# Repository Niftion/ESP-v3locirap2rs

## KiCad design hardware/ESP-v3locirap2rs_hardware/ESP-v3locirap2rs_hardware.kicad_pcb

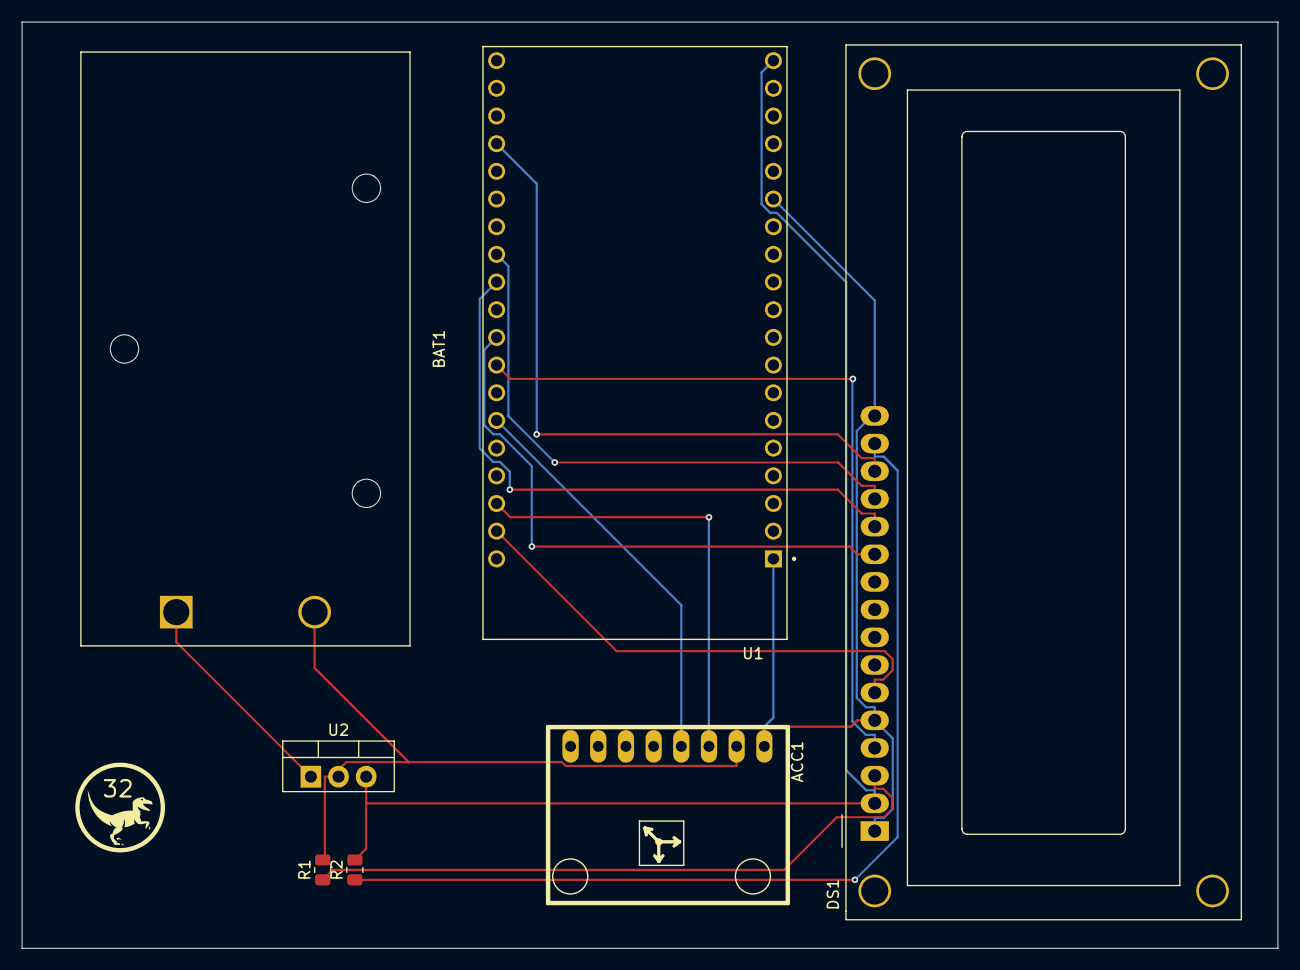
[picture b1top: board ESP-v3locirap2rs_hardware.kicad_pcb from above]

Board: 2 copper layers, 115.2 x 85.0 mm, 7 parts (0 on the bottom side), 14 nets.

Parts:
ACC1: GY-521
BAT1: BC9VPC; BatteryHolder_Eagle_12BH611-GR
DS1: WC1602A
R1: 1k; R_0805_2012Metric
R2: 1.2k; R_0805_2012Metric
U1: ESP32-DEVKITC-32D; MODULE_ESP32-DEVKITC-32D
U2: L7805CV; TO-220-3_Vertical

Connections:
/ESP32/3.3V: ACC1.VCC, U1.J2-1 (3V3)
/ESP32/5V: DS1.2 (VDD), R2.2, U1.J2-19 (EXT_5V), U2.3 (OUT)
/ESP32/Pin 15: DS1.14 (D7), U1.J3-16 (IO15)
/ESP32/Pin 16: DS1.13 (D6), U1.J3-12 (IO16)
/ESP32/Pin 17: DS1.12 (D5), U1.J3-11 (IO17)
/ESP32/Pin 18: DS1.11 (D4), U1.J3-9 (IO18)
/ESP32/Pin 19: DS1.4 (RS), U1.J3-8 (IO19)
/ESP32/Pin 23: DS1.6 (E), U1.J3-2 (IO23)
/ESP32/SCL: ACC1.SCL, U1.J3-3 (IO22)
/ESP32/SDA: ACC1.SDA, U1.J3-6 (IO21)
GND: ACC1.GND, BAT1.2, DS1.1 (VSS), DS1.5 (R/W), DS1.16 (LED(-)), R1.2, U1.J2-14 (GND1), U2.2 (GND)
unnamed: DS1.15 (LED(+)), R2.1
unnamed: DS1.3 (VO), R1.1
unnamed: BAT1.1, U2.1 (IN)

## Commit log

2024-11-22 first
2024-11-22 placeholder2
2024-11-22 yayaya
2024-11-22 platformIO init
2024-11-22 theretailstore
    \\ 0 ,_, X ?
2024-11-22 kicad init
2024-11-22 stm32 file setup
2024-11-22 awawa
2024-11-22 directory changes
2024-11-22 gitignore
2024-11-22 symbol updates
2024-11-22 directory fix
2024-11-22 gitignore updates
2024-11-22 Remove ignored files from repository
2024-11-22 wheee
2024-11-22 gyroscope updates
2024-11-22 changed keycad path?
2024-11-22 hjllhuk
2024-11-22 blinking light code
2024-11-22 kicad directory fix
2024-11-22 added driver folder
2024-11-22 circuit diagrams
2024-11-22 kicad schematic updates
2024-11-22 pcb updates
2024-11-22 accelerometer code, probably incorrect values displayed
2024-11-22 circuit wiring
2024-11-22 kicad pcb updates
2024-11-22 moving stuff
2024-11-22 more re-arranging folder hierarchy lolol
2024-11-22 pcb v1 completed
    added cool velociraptor graphic too (rawr)
2024-11-22 Update main.cpp
    fixed comments
2024-12-01 cleaned up code and added in LCD display
2024-12-03 schematic finalization
2024-12-03 PCB completed
2024-12-03 pcb & schematic updates
2024-12-03 schematic updates
2024-12-03 backups
